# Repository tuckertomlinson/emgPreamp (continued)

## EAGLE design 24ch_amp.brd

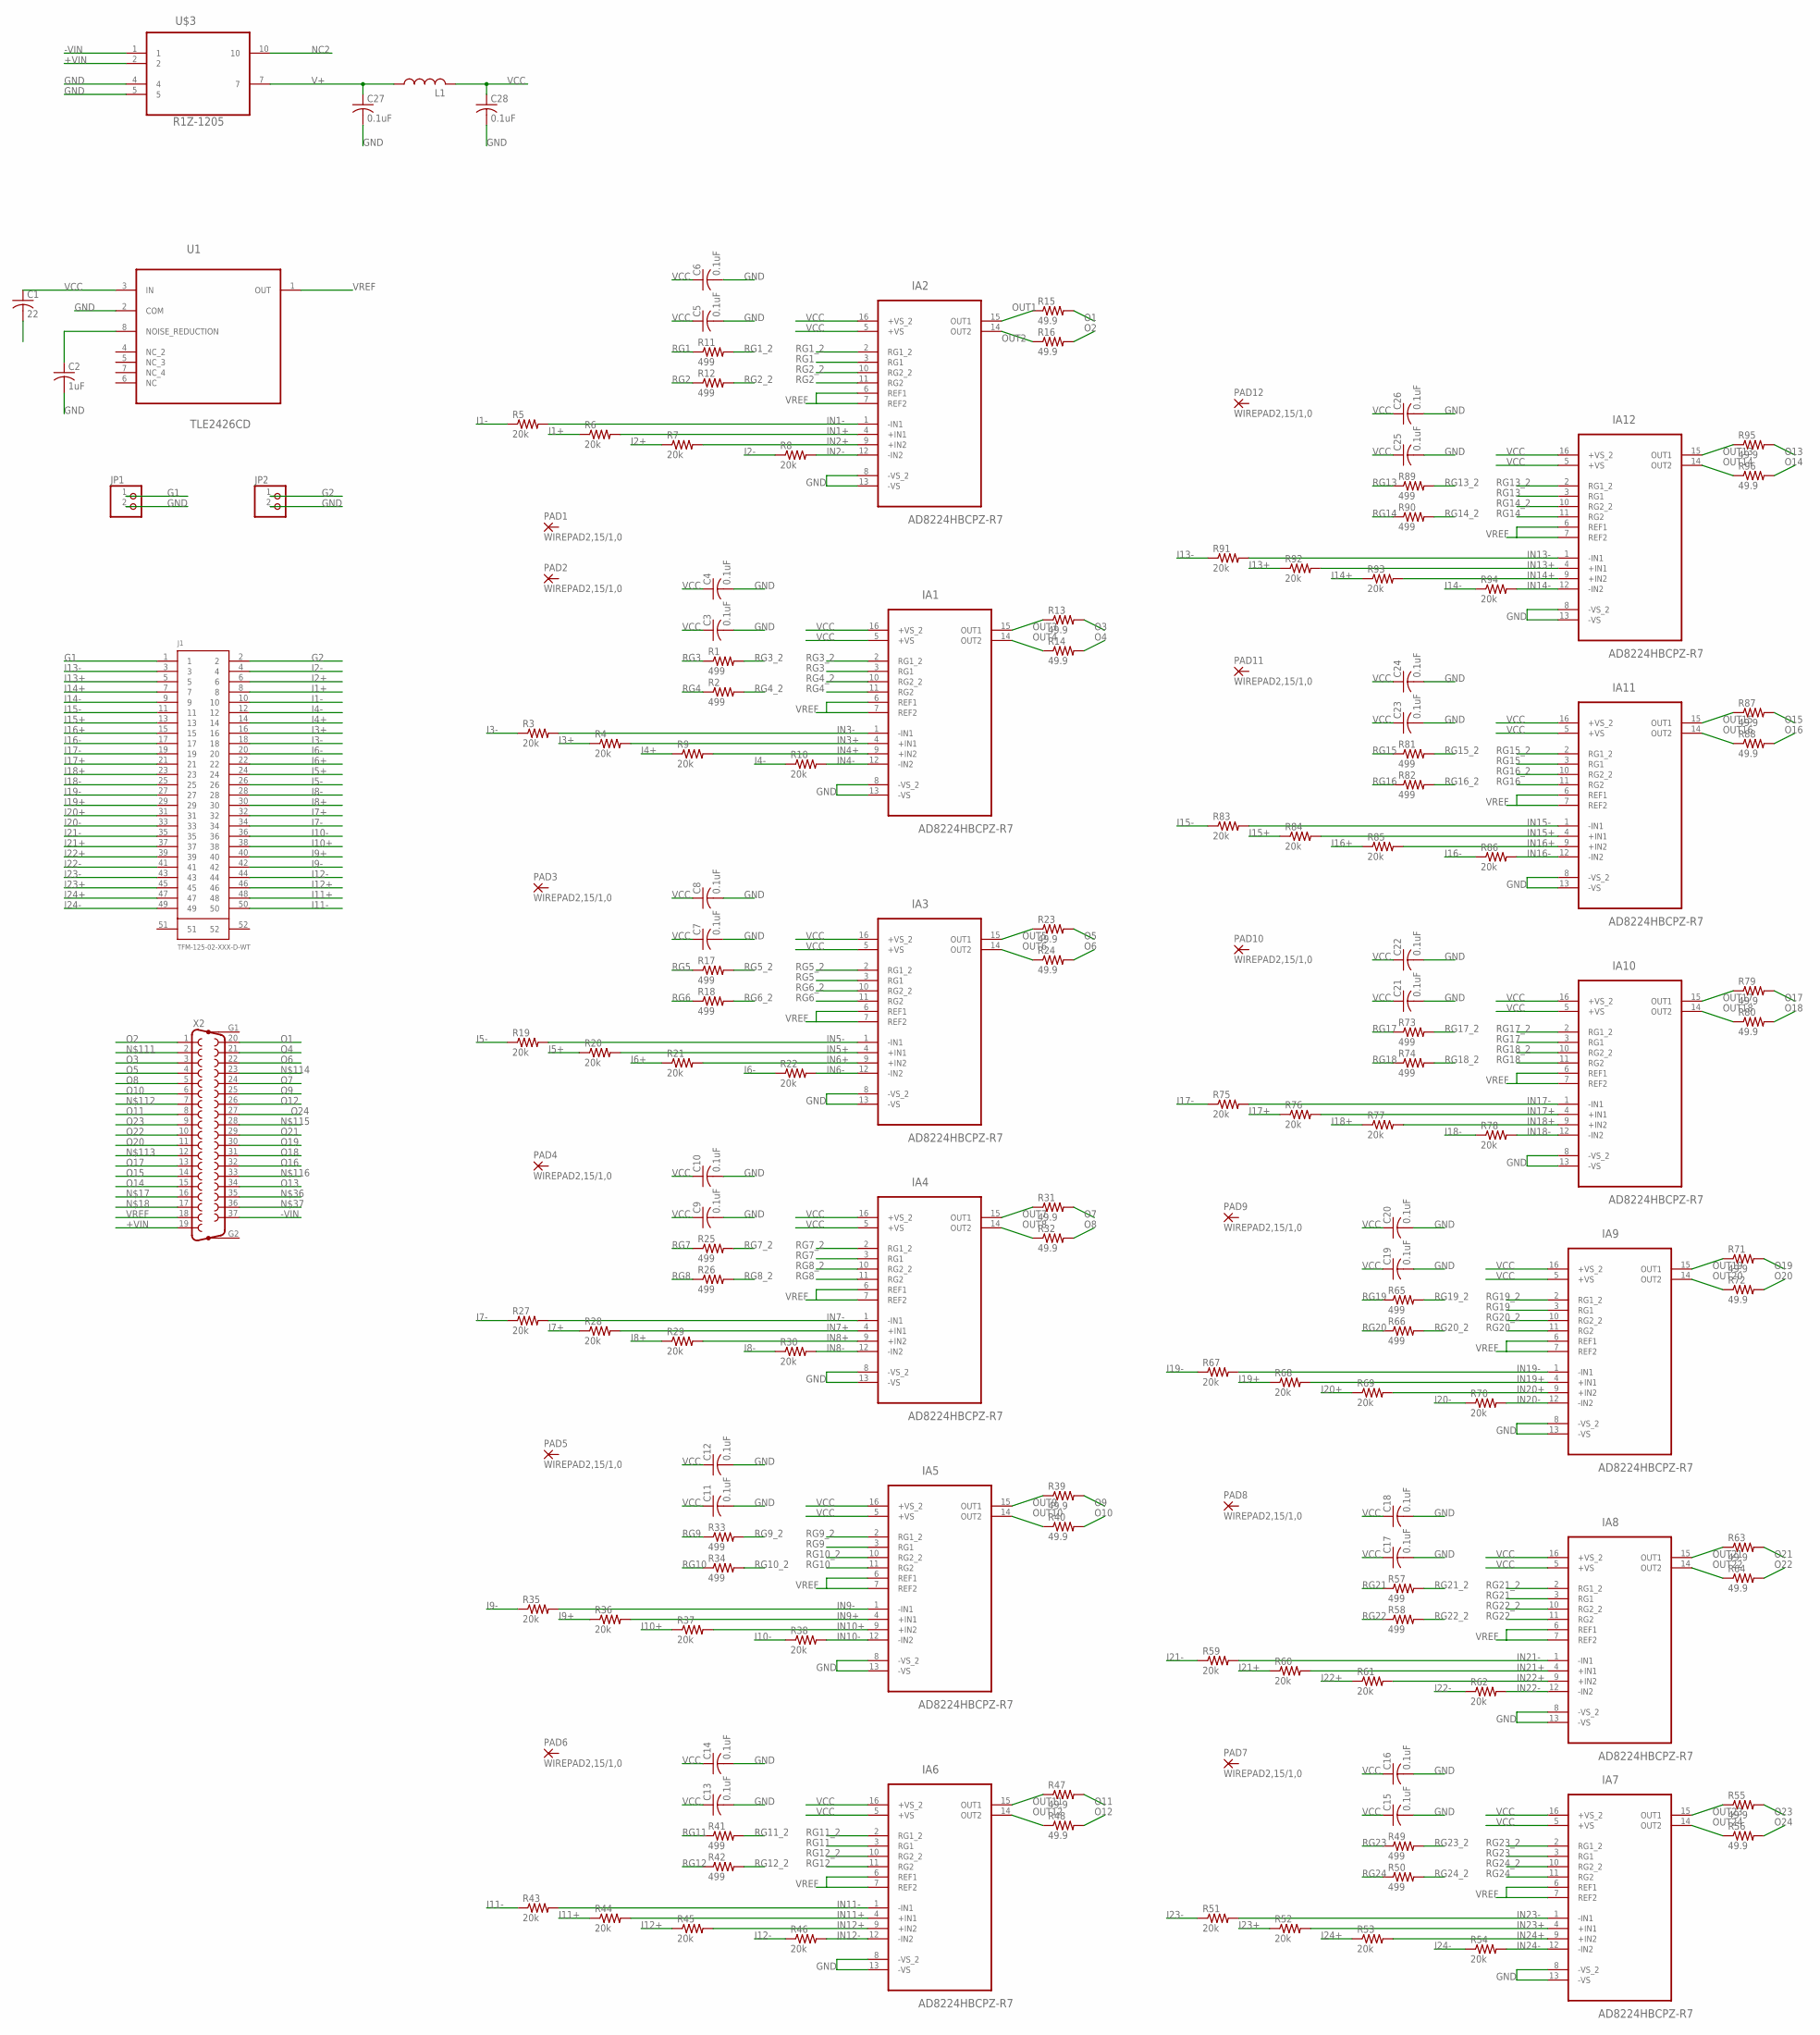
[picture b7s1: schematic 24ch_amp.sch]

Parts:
C1: 22; C0805
C2: 1uF; C0805
C3, C4, C5, C6, C7, C8, C9, C10, C11, C12, C13, C14, C15, C16, C17, C18, C19, C20, C21, C22, C23, C24, C25, C26, C27, C28: 0.1uF; C0805
IA1, IA2, IA3, IA4, IA5, IA6, IA7, IA8, IA9, IA10, IA11, IA12: AD8224HBCPZ-R7; QFN65P400X400X100-16N
J1: TFM-125-02-XXX-D-WT
JP1, JP2: PINHD-1X2; 1X02
L1: L-USL3225M; L3225M
PAD1, PAD2, PAD3, PAD4, PAD5, PAD6, PAD7, PAD8, PAD9, PAD10, PAD11, PAD12: WIREPAD2,15/1,0; 2,15/1,0
R1, R2, R11, R12, R17, R18, R25, R26, R33, R34, R41, R42, R49, R50, R57, R58, R65, R66, R73, R74, R81, R82, R89, R90: 499; R0805
R3, R4, R5, R6, R7, R8, R9, R10, R19, R20, R21, R22, R27, R28, R29, R30, R35, R36, R37, R38, R43, R44, R45, R46, R51, R52, R53, R54, R59, R60, R61, R62, R67, R68, R69, R70, R75, R76, R77, R78, R83, R84, R85, R86, R91, R92, R93, R94: 20k; R0805
R13, R14, R15, R16, R23, R24, R31, R32, R39, R40, R47, R48, R55, R56, R63, R64, R71, R72, R79, R80, R87, R88, R95, R96: 49.9; R0805
U1: TLE2426CD; SOIC127P600X175-8N
U$3: R1Z-1205
X2: F37HP

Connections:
+VIN: U$3.2, X2.19
-VIN: U$3.1, X2.37
G1: J1.1, JP1.1
G2: J1.2, JP2.1
GND: C1.2, C2.2, C3.2, C4.2, C5.2, C6.2, C7.2, C8.2, C9.2, C10.2, C11.2, C12.2, C13.2, C14.2, C15.2, C16.2, C17.2, C18.2, C19.2, C20.2, C21.2, C22.2, C23.2, C24.2, C25.2, C26.2, C27.2, C28.2, IA1.8 (-VS_2), IA1.13 (-VS), IA2.8 (-VS_2), IA2.13 (-VS), IA3.8 (-VS_2), IA3.13 (-VS), IA4.8 (-VS_2), IA4.13 (-VS), IA5.8 (-VS_2), IA5.13 (-VS), IA6.8 (-VS_2), IA6.13 (-VS), IA7.8 (-VS_2), IA7.13 (-VS), IA8.8 (-VS_2), IA8.13 (-VS), IA9.8 (-VS_2), IA9.13 (-VS), IA10.8 (-VS_2), IA10.13 (-VS), IA11.8 (-VS_2), IA11.13 (-VS), IA12.8 (-VS_2), IA12.13 (-VS), JP1.2, JP2.2, U1.2 (COM), U$3.4, U$3.5
I1+: J1.8, R6.1
I1-: J1.10, R5.1
I2+: J1.6, R7.1
I2-: J1.4, R8.1
I3+: J1.16, R4.1
I3-: J1.18, R3.1
I4+: J1.14, R9.1
I4-: J1.12, R10.1
I5+: J1.24, R20.1
I5-: J1.26, R19.1
I6+: J1.22, R21.1
I6-: J1.20, R22.1
I7+: J1.32, R28.1
I7-: J1.34, R27.1
I8+: J1.30, R29.1
I8-: J1.28, R30.1
I9+: J1.40, R36.1
I9-: J1.42, R35.1
I10+: J1.38, R37.1
I10-: J1.36, R38.1
I11+: J1.48, R44.1
I11-: J1.50, R43.1
I12+: J1.46, R45.1
I12-: J1.44, R46.1
I13+: J1.5, R92.1
I13-: J1.3, R91.1
I14+: J1.7, R93.1
I14-: J1.9, R94.1
I15+: J1.13, R84.1
I15-: J1.11, R83.1
I16+: J1.15, R85.1
I16-: J1.17, R86.1
I17+: J1.21, R76.1
I17-: J1.19, R75.1
I18+: J1.23, R77.1
I18-: J1.25, R78.1
I19+: J1.29, R68.1
I19-: J1.27, R67.1
I20+: J1.31, R69.1
I20-: J1.33, R70.1
I21+: J1.37, R60.1
I21-: J1.35, R59.1
I22+: J1.39, R61.1
I22-: J1.41, R62.1
I23+: J1.45, R52.1
I23-: J1.43, R51.1
I24+: J1.47, R53.1
I24-: J1.49, R54.1
IN1+: IA2.4 (+IN1), R6.2
IN1-: IA2.1 (-IN1), R5.2
IN2+: IA2.9 (+IN2), R7.2
IN2-: IA2.12 (-IN2), R8.2
IN3+: IA1.4 (+IN1), R4.2
IN3-: IA1.1 (-IN1), R3.2
IN4+: IA1.9 (+IN2), R9.2
IN4-: IA1.12 (-IN2), R10.2
IN5+: IA3.4 (+IN1), R20.2
IN5-: IA3.1 (-IN1), R19.2
IN6+: IA3.9 (+IN2), R21.2
IN6-: IA3.12 (-IN2), R22.2
IN7+: IA4.4 (+IN1), R28.2
IN7-: IA4.1 (-IN1), R27.2
IN8+: IA4.9 (+IN2), R29.2
IN8-: IA4.12 (-IN2), R30.2
IN9+: IA5.4 (+IN1), R36.2
IN9-: IA5.1 (-IN1), R35.2
IN10+: IA5.9 (+IN2), R37.2
IN10-: IA5.12 (-IN2), R38.2
IN11+: IA6.4 (+IN1), R44.2
IN11-: IA6.1 (-IN1), R43.2
IN12+: IA6.9 (+IN2), R45.2
IN12-: IA6.12 (-IN2), R46.2
IN13+: IA12.4 (+IN1), R92.2
IN13-: IA12.1 (-IN1), R91.2
IN14+: IA12.9 (+IN2), R93.2
IN14-: IA12.12 (-IN2), R94.2
IN15+: IA11.4 (+IN1), R84.2
IN15-: IA11.1 (-IN1), R83.2
IN16+: IA11.9 (+IN2), R85.2
IN16-: IA11.12 (-IN2), R86.2
IN17+: IA10.4 (+IN1), R76.2
IN17-: IA10.1 (-IN1), R75.2
IN18+: IA10.9 (+IN2), R77.2
IN18-: IA10.12 (-IN2), R78.2
IN19+: IA9.4 (+IN1), R68.2
IN19-: IA9.1 (-IN1), R67.2
IN20+: IA9.9 (+IN2), R69.2
IN20-: IA9.12 (-IN2), R70.2
IN21+: IA8.4 (+IN1), R60.2
IN21-: IA8.1 (-IN1), R59.2
IN22+: IA8.9 (+IN2), R61.2
IN22-: IA8.12 (-IN2), R62.2
IN23+: IA7.4 (+IN1), R52.2
IN23-: IA7.1 (-IN1), R51.2
IN24+: IA7.9 (+IN2), R53.2
IN24-: IA7.12 (-IN2), R54.2
unnamed: C2.1, U1.8 (NOISE_REDUCTION)
NC2: U$3.10
O1: R15.2, X2.20
O2: R16.2, X2.1
O3: R13.2, X2.3
O4: R14.2, X2.21
O5: R23.2, X2.4
O6: R24.2, X2.22
O7: R31.2, X2.24
O8: R32.2, X2.5
O9: R39.2, X2.25
O10: R40.2, X2.6
O11: R47.2, X2.8
O12: R48.2, X2.26
O13: R95.2, X2.34
O14: R96.2, X2.15
O15: R87.2, X2.14
O16: R88.2, X2.32
O17: R79.2, X2.13
O18: R80.2, X2.31
O19: R71.2, X2.30
O20: R72.2, X2.11
O21: R63.2, X2.29
O22: R64.2, X2.10
O23: R55.2, X2.9
O24: R56.2, X2.27
OUT1: IA2.15 (OUT1), R15.1
OUT2: IA2.14 (OUT2), R16.1
OUT3: IA1.15 (OUT1), R13.1
OUT4: IA1.14 (OUT2), R14.1
OUT5: IA3.15 (OUT1), R23.1
OUT6: IA3.14 (OUT2), R24.1
OUT7: IA4.15 (OUT1), R31.1
OUT8: IA4.14 (OUT2), R32.1
OUT9: IA5.15 (OUT1), R39.1
OUT10: IA5.14 (OUT2), R40.1
OUT11: IA6.15 (OUT1), R47.1
OUT12: IA6.14 (OUT2), R48.1
OUT13: IA12.15 (OUT1), R95.1
OUT14: IA12.14 (OUT2), R96.1
OUT15: IA11.15 (OUT1), R87.1
OUT16: IA11.14 (OUT2), R88.1
OUT17: IA10.15 (OUT1), R79.1
OUT18: IA10.14 (OUT2), R80.1
OUT19: IA9.15 (OUT1), R71.1
OUT20: IA9.14 (OUT2), R72.1
OUT21: IA8.15 (OUT1), R63.1
OUT22: IA8.14 (OUT2), R64.1
OUT23: IA7.15 (OUT1), R55.1
OUT24: IA7.14 (OUT2), R56.1
RG1: IA2.3 (RG1), R11.1
RG1_2: IA2.2 (RG1_2), R11.2
RG2: IA2.11 (RG2), R12.1
RG2_2: IA2.10 (RG2_2), R12.2
RG3: IA1.3 (RG1), R1.1
RG3_2: IA1.2 (RG1_2), R1.2
RG4: IA1.11 (RG2), R2.1
RG4_2: IA1.10 (RG2_2), R2.2
RG5: IA3.3 (RG1), R17.1
RG5_2: IA3.2 (RG1_2), R17.2
RG6: IA3.11 (RG2), R18.1
RG6_2: IA3.10 (RG2_2), R18.2
RG7: IA4.3 (RG1), R25.1
RG7_2: IA4.2 (RG1_2), R25.2
RG8: IA4.11 (RG2), R26.1
RG8_2: IA4.10 (RG2_2), R26.2
RG9: IA5.3 (RG1), R33.1
RG9_2: IA5.2 (RG1_2), R33.2
RG10: IA5.11 (RG2), R34.1
RG10_2: IA5.10 (RG2_2), R34.2
RG11: IA6.3 (RG1), R41.1
RG11_2: IA6.2 (RG1_2), R41.2
RG12: IA6.11 (RG2), R42.1
RG12_2: IA6.10 (RG2_2), R42.2
RG13: IA12.3 (RG1), R89.1
RG13_2: IA12.2 (RG1_2), R89.2
RG14: IA12.11 (RG2), R90.1
RG14_2: IA12.10 (RG2_2), R90.2
RG15: IA11.3 (RG1), R81.1
RG15_2: IA11.2 (RG1_2), R81.2
RG16: IA11.11 (RG2), R82.1
RG16_2: IA11.10 (RG2_2), R82.2
RG17: IA10.3 (RG1), R73.1
RG17_2: IA10.2 (RG1_2), R73.2
RG18: IA10.11 (RG2), R74.1
RG18_2: IA10.10 (RG2_2), R74.2
RG19: IA9.3 (RG1), R65.1
RG19_2: IA9.2 (RG1_2), R65.2
RG20: IA9.11 (RG2), R66.1
RG20_2: IA9.10 (RG2_2), R66.2
RG21: IA8.3 (RG1), R57.1
RG21_2: IA8.2 (RG1_2), R57.2
RG22: IA8.11 (RG2), R58.1
RG22_2: IA8.10 (RG2_2), R58.2
RG23: IA7.3 (RG1), R49.1
RG23_2: IA7.2 (RG1_2), R49.2
RG24: IA7.11 (RG2), R50.1
RG24_2: IA7.10 (RG2_2), R50.2
V+: C27.1, L1.1, U$3.7
VCC: C1.1, C3.1, C4.1, C5.1, C6.1, C7.1, C8.1, C9.1, C10.1, C11.1, C12.1, C13.1, C14.1, C15.1, C16.1, C17.1, C18.1, C19.1, C20.1, C21.1, C22.1, C23.1, C24.1, C25.1, C26.1, C28.1, IA1.5 (+VS), IA1.16 (+VS_2), IA2.5 (+VS), IA2.16 (+VS_2), IA3.5 (+VS), IA3.16 (+VS_2), IA4.5 (+VS), IA4.16 (+VS_2), IA5.5 (+VS), IA5.16 (+VS_2), IA6.5 (+VS), IA6.16 (+VS_2), IA7.5 (+VS), IA7.16 (+VS_2), IA8.5 (+VS), IA8.16 (+VS_2), IA9.5 (+VS), IA9.16 (+VS_2), IA10.5 (+VS), IA10.16 (+VS_2), IA11.5 (+VS), IA11.16 (+VS_2), IA12.5 (+VS), IA12.16 (+VS_2), L1.2, U1.3 (IN)
VREF: IA1.6 (REF1), IA1.7 (REF2), IA2.6 (REF1), IA2.7 (REF2), IA3.6 (REF1), IA3.7 (REF2), IA4.6 (REF1), IA4.7 (REF2), IA5.6 (REF1), IA5.7 (REF2), IA6.6 (REF1), IA6.7 (REF2), IA7.6 (REF1), IA7.7 (REF2), IA8.6 (REF1), IA8.7 (REF2), IA9.6 (REF1), IA9.7 (REF2), IA10.6 (REF1), IA10.7 (REF2), IA11.6 (REF1), IA11.7 (REF2), IA12.6 (REF1), IA12.7 (REF2), U1.1 (OUT), X2.18

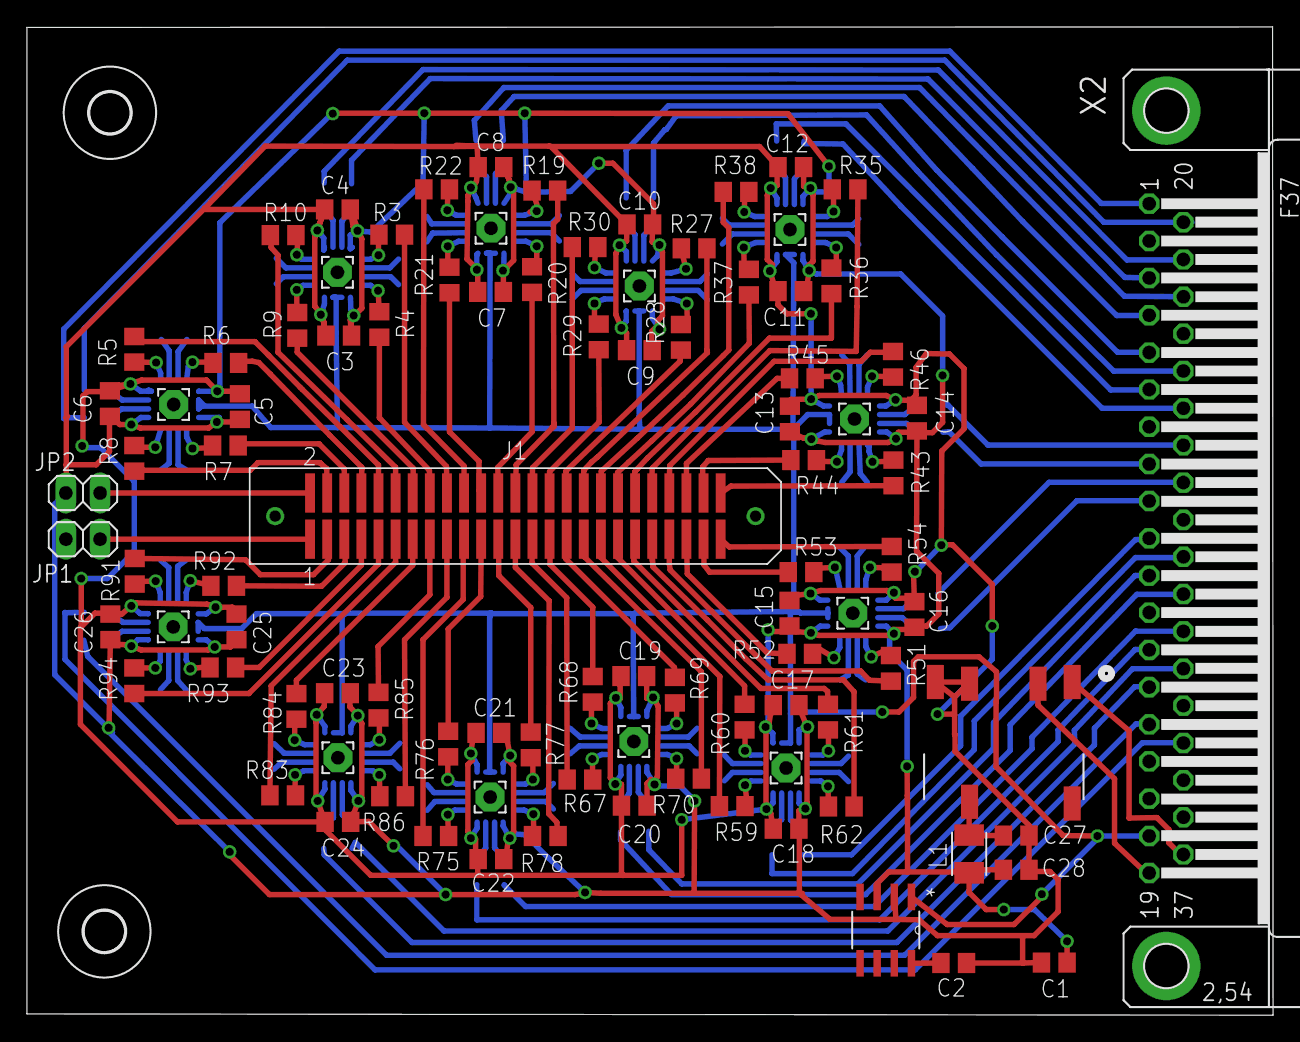
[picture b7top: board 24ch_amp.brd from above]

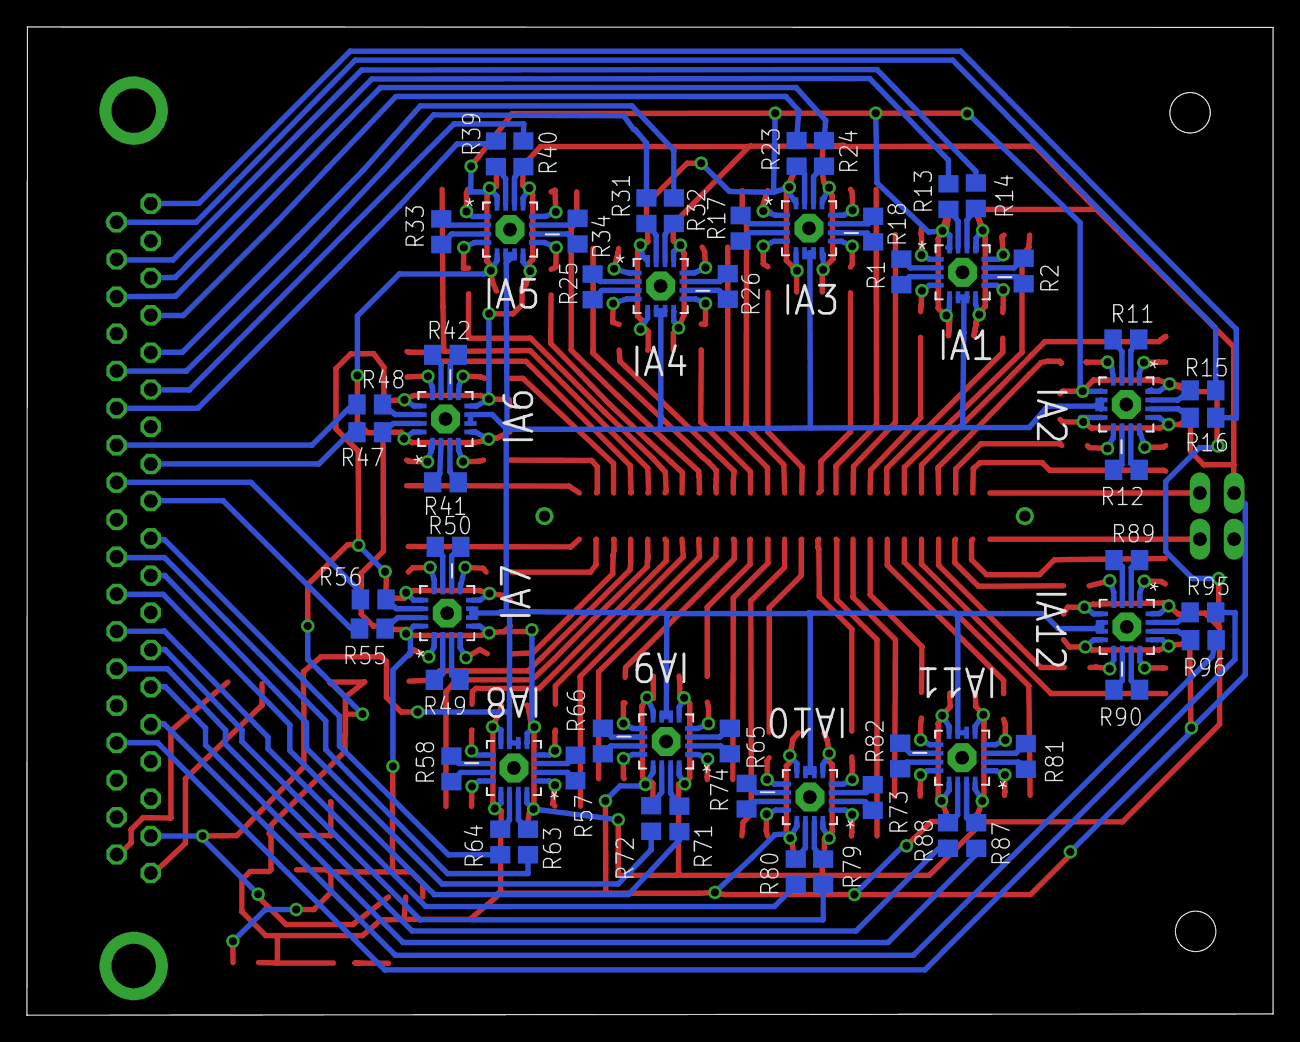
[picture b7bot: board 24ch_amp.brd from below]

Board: 2 copper layers, 92.5 x 73.4 mm, 157 parts (60 on the bottom side), 201 nets.

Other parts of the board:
U$1, U$2: 3,0

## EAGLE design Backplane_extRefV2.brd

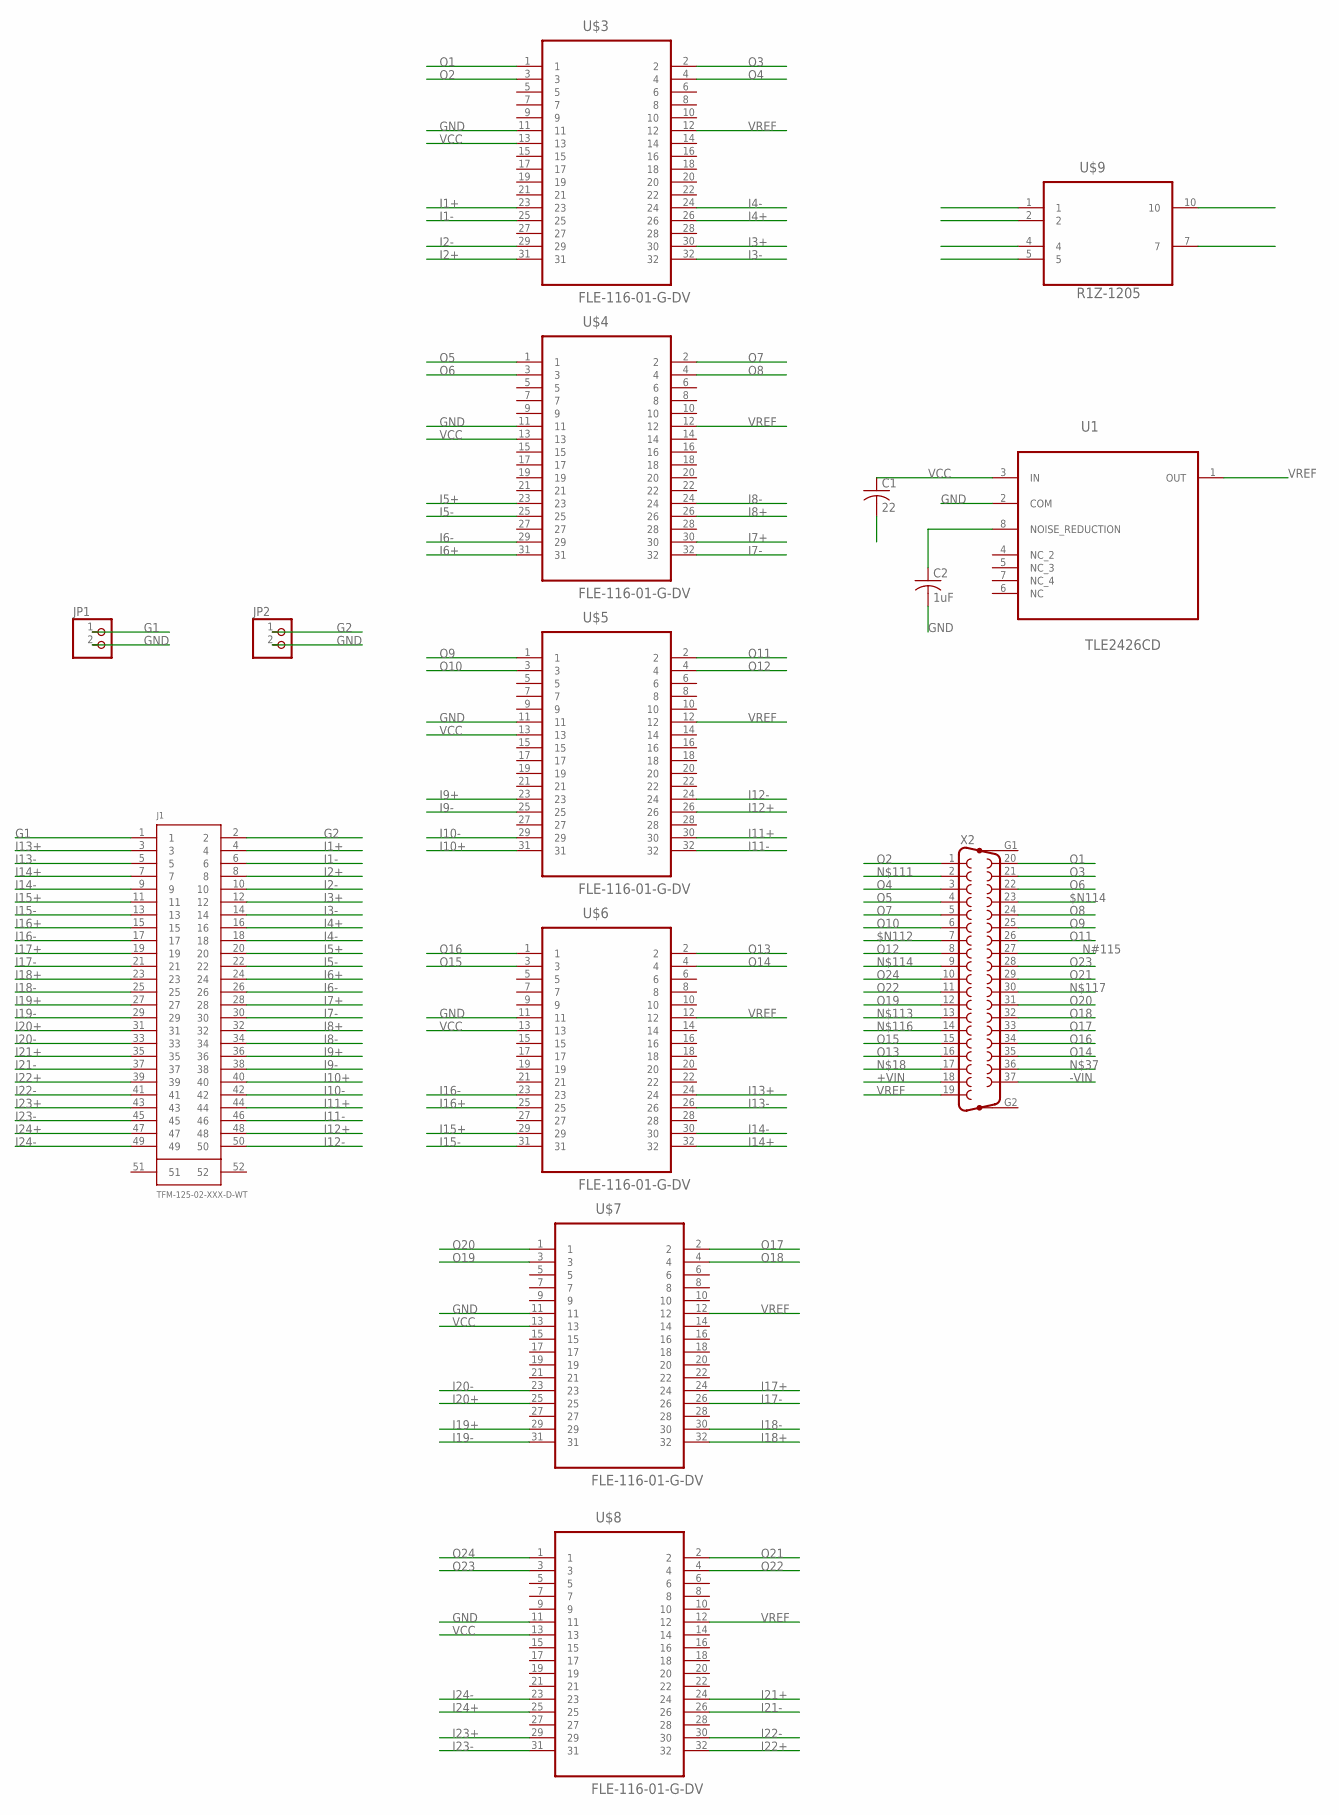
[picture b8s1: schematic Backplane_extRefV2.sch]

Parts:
C1: 22; C0805
C2: 1uF; C0805
J1: TFM-125-02-XXX-D-WT
JP1, JP2: PINHD-1X2; 1X02
U1: TLE2426CD; SOIC127P600X175-8N
U$3, U$4, U$5, U$6, U$7, U$8: FLE-116-01-G-DV; SAMTEC_FLE-116-01-G-DV
U$9: R1Z-1205
X2: F37HP

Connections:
$N112: X2.7
$N114: X2.23
+VIN: U$9.2, X2.18
-VIN: U$9.1, X2.37
G1: J1.1, JP1.1
G2: J1.2, JP2.1
GND: C1.2, C2.2, JP1.2, JP2.2, U1.2 (COM), U$3.11, U$4.11, U$5.11, U$6.11, U$7.11, U$8.11, U$9.4, U$9.5
I1+: J1.4, U$3.23
I1-: J1.6, U$3.25
I2+: J1.8, U$3.31
I2-: J1.10, U$3.29
I3+: J1.12, U$3.30
I3-: J1.14, U$3.32
I4+: J1.16, U$3.26
I4-: J1.18, U$3.24
I5+: J1.20, U$4.23
I5-: J1.22, U$4.25
I6+: J1.24, U$4.31
I6-: J1.26, U$4.29
I7+: J1.28, U$4.30
I7-: J1.30, U$4.32
I8+: J1.32, U$4.26
I8-: J1.34, U$4.24
I9+: J1.36, U$5.23
I9-: J1.38, U$5.25
I10+: J1.40, U$5.31
I10-: J1.42, U$5.29
I11+: J1.44, U$5.30
I11-: J1.46, U$5.32
I12+: J1.48, U$5.26
I12-: J1.50, U$5.24
I13+: J1.3, U$6.24
I13-: J1.5, U$6.26
I14+: J1.7, U$6.32
I14-: J1.9, U$6.30
I15+: J1.11, U$6.29
I15-: J1.13, U$6.31
I16+: J1.15, U$6.25
I16-: J1.17, U$6.23
I17+: J1.19, U$7.24
I17-: J1.21, U$7.26
I18+: J1.23, U$7.32
I18-: J1.25, U$7.30
I19+: J1.27, U$7.29
I19-: J1.29, U$7.31
I20+: J1.31, U$7.25
I20-: J1.33, U$7.23
I21+: J1.35, U$8.24
I21-: J1.37, U$8.26
I22+: J1.39, U$8.32
I22-: J1.41, U$8.30
I23+: J1.43, U$8.29
I23-: J1.45, U$8.31
I24+: J1.47, U$8.25
I24-: J1.49, U$8.23
N#115: X2.27
unnamed: C2.1, U1.8 (NOISE_REDUCTION)
NC2: U$9.10
O1: U$3.1, X2.20
O2: U$3.3, X2.1
O3: U$3.2, X2.21
O4: U$3.4, X2.3
O5: U$4.1, X2.4
O6: U$4.3, X2.22
O7: U$4.2, X2.5
O8: U$4.4, X2.24
O9: U$5.1, X2.25
O10: U$5.3, X2.6
O11: U$5.2, X2.26
O12: U$5.4, X2.8
O13: U$6.2, X2.16
O14: U$6.4, X2.35
O15: U$6.3, X2.15
O16: U$6.1, X2.34
O17: U$7.2, X2.33
O18: U$7.4, X2.32
O19: U$7.3, X2.12
O20: U$7.1, X2.31
O21: U$8.2, X2.29
O22: U$8.4, X2.11
O23: U$8.3, X2.28
O24: U$8.1, X2.10
VCC: C1.1, U1.3 (IN), U$3.13, U$4.13, U$5.13, U$6.13, U$7.13, U$8.13, U$9.7
VREF: U1.1 (OUT), U$3.12, U$4.12, U$5.12, U$6.12, U$7.12, U$8.12, X2.19

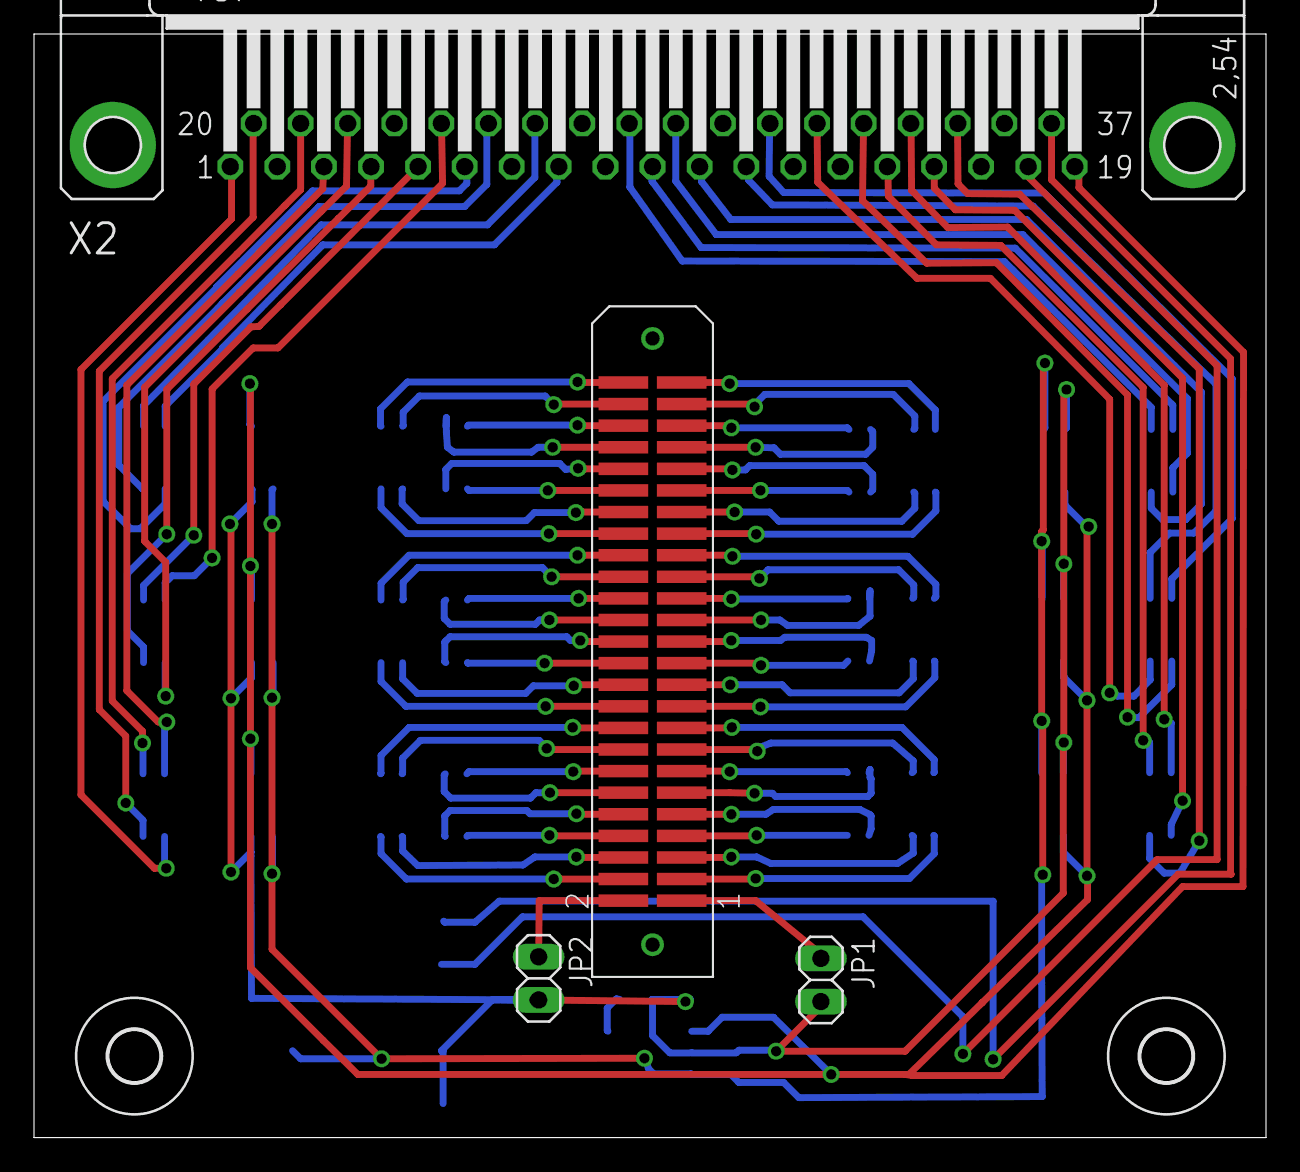
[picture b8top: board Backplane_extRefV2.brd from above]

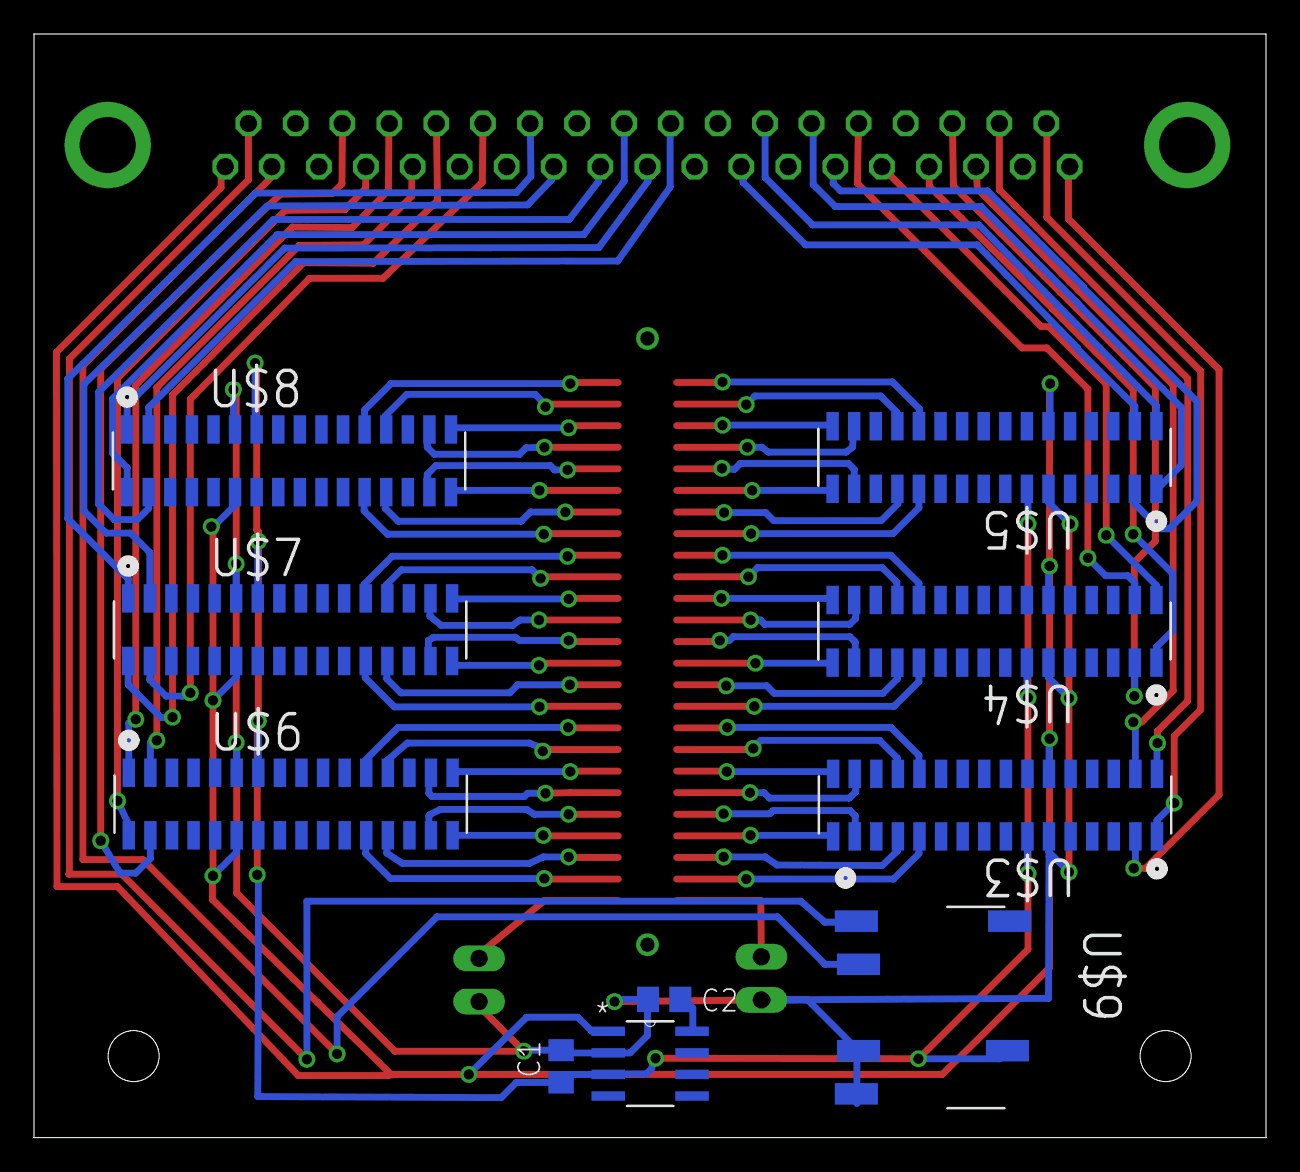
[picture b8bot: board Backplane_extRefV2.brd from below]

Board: 2 copper layers, 72.5 x 64.9 mm, 16 parts (10 on the bottom side), 80 nets.

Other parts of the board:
U$1, U$2: 3,0

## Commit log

2016-08-04 added initial boards to repo. Have amp card with/without internal ref line. Have backplanes for with/without internal refs. Have single board solution with all amps on board. None of the current desi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
2016-08-04 added a gitignore file to filter irrelevant things like eagle's old save files from the repo
2016-08-04 added readme.txt
2016-08-16 minor updates to routing. Added DC-DC voltage converter/isolator to backplaneV2 & 24ch brd
2016-08-18 added new designs that use .1in pitch rather than.05, and added DC-DC isolator for VCC input to backplane
2016-08-20 added card to convert 12v DC into isolated 5V & 2.5V DC, including filtering for switching artifacts
2016-08-29 reorganized IO labeling to be consistent on v4 backplane
2016-09-01 new preamp board with capacitive input coupling
2016-09-01 routing improvements- attempting to isolate inputs from outputs better
2016-12-24 updated power board designs: v2 uses low current 2.5v reference, v3 uses 10v rail and 5v ref both with simple linear regulators. Added breakout board to go from DB37 to BNC
2017-01-25 removed old schematics. Updated readme
2017-01-25 updated V4 powerboard to actually include switchmode pads. Added BOM for backplane and daughter card
2017-01-25 added powerboard BOM
2017-02-24 minor labeling and component placement updates. most significant is correcting part position on powerboard so 22uF bypass cap actually connects to ground.
2017-07-27 added pdf schematics
2017-08-01 updated design to add RF lowpass and decoupling to input. Also added real ground plane and VREF plane to help isolate inputs from noise
2017-08-01 updated pdf schematic to match new layout
2017-08-01 updated BOM for daughter cards to include new passives for input filtering
2017-08-02 minor routing changes to increase VREF plane coverage
2017-08-02 updated RF input suppression to include decoupling caps to gnd
